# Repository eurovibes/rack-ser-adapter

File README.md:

<!-- SPDX-FileCopyrightText: 2021 Benedikt Spranger <b.spranger@linutronix.de> -->
<!-- SPDX-License-Identifier: CERN-OHL-S-2.0 -->

# rack-ser-adapter -  RS232 DE-9 to EIA-561 RJ45 adapter

## Adapter pinout (EIA-561)

### 1:1

| DB-9 Pin | Signal	| RJ45 |
|---------:|--------|-----:|
1 | DCD | 2
2 | RxD | 5
3 | TxD | 6
4 | DTR | 3
5 | GND | 4
6 | DSR | 1
7 | RTS | 8
8 | CTS | 7
9 |  -  | -

### CROSSOVER / NULLMODEM

| RJ45 | Signal	| DB-9 Pin |
|-----:|--------|---------:|
1 | DTR | 4
2 | DCD | -
3 | DST | 6
4 | GND | 5
5 | TxD | 3
6 | RxD | 2
7 | RTS | 7
8 | CTS | 8
9 |  -  | -

## License rules

rack-ser-adapter is provided under the terms of the CERN-OHL-S license
version 2 as provided in the LICENSES/CERN-OHL-S-2.0 file.

Instead of adding license boilerplates to the individual files,
rack-ser-adapter uses SPDX license identifiers, which are machine parseable
and considered legaly equivalent.

The SPDX license identifier in rack-ser-adapter shall be added at the first
possible line in a file which can contain a comment. This is normally the
first line except for scripts. Scripts require the #!PATH_TO_INTERPRETER tag
in the first line; place the SPDX identifier into the second line.

The SPDX license identifier is added in form of a comment.

## Copyright and License

> Copyright Benedikt Spranger 2021.
> This source describes Open Hardware and is licensed under the CERNOHL-S v2.
> You may redistribute and modify this source and make products using it
> under the terms of the CERN-OHL-S v2 (https://ohwr.org/cern ohl s v2.txt ).
> This source is distributed WITHOUT ANY EXPRESS OR IMPLIED WARRANTY, INCLUDING
> OF MERCHANTABILITY, SATISFACTORY QUALITY AND FITNESS FOR A PARTICULAR PURPOSE.
> Please see the CERN-OHL-S v2 for applicable conditions.
> Source location: https://github.com/eurovibes/rack-ser-adapter
> As per CERN-OHL-S v2 section 4, should You produce hardware based
> on this source, You must where practicable maintain the Source Location
> visible on the external case of the rack-ser-adapter or other products you
> make using this source.

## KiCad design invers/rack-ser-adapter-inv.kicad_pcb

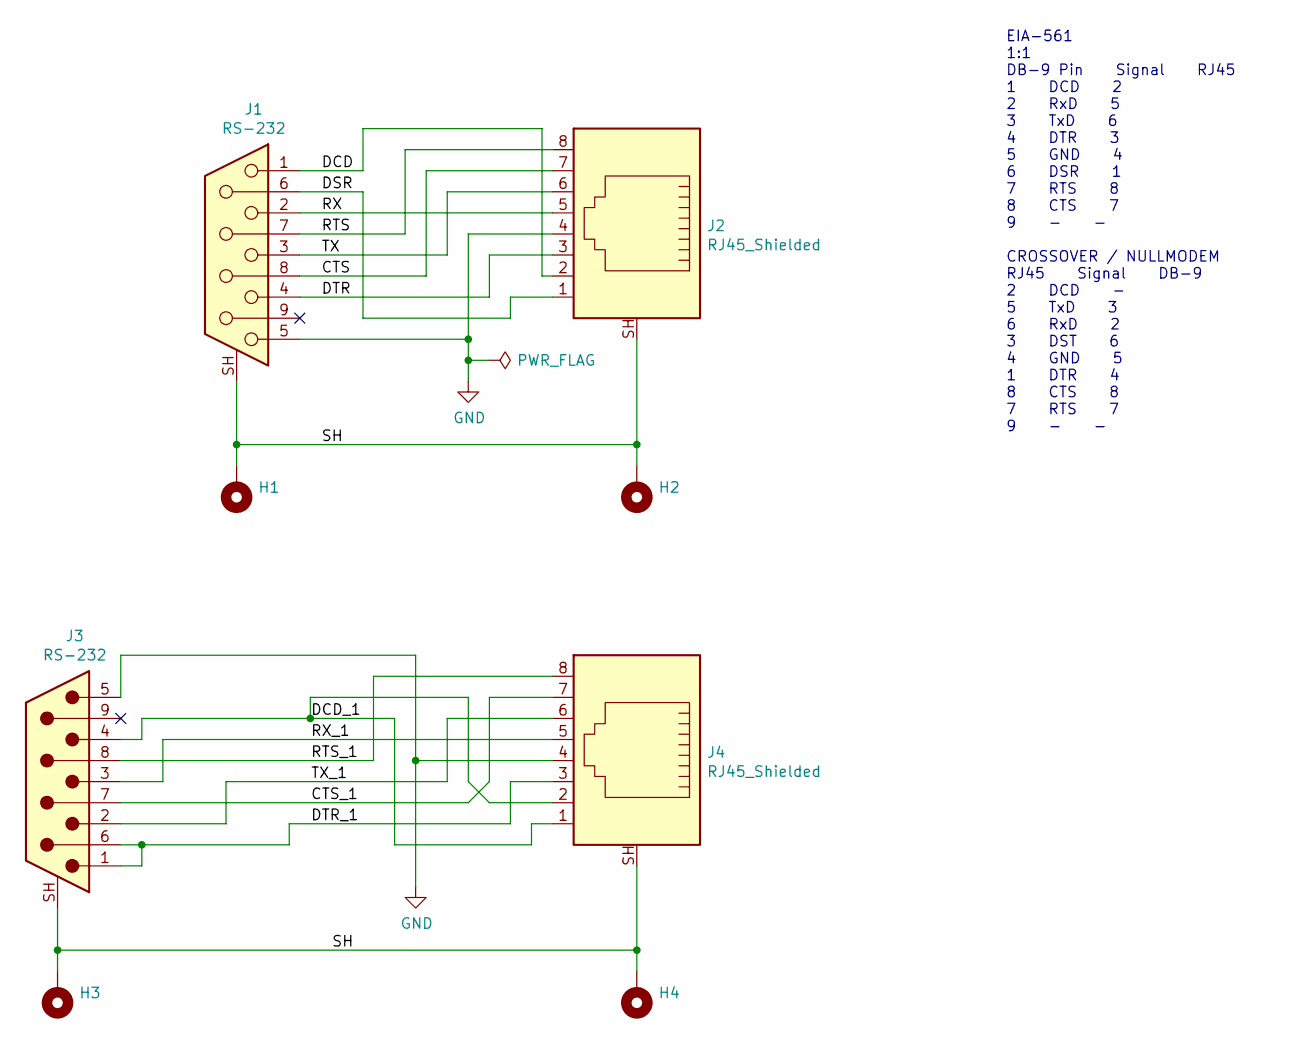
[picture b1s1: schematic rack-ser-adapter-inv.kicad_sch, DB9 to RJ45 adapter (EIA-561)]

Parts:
H1, H2, H3, H4: MountingHole_3.2mm_M3_ISO7380_Pad
J1: RS-232; DSUB-9_Female_Horizontal_P2.77x2.84mm_EdgePinOffset4.94mm_H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; ManuPart# A-DF 09 A/KG-T4S
J2, J4: RJ45_Shielded; RJ45_Ninigi_GE; ManuPart# MTJ-889X1-FSE
J3: RS-232; DSUB-9_Male_Horizontal_P2.77x2.84mm_EdgePinOffset4.94mm_Hou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; ManuPart# A-DS 09 A/KG-T4S

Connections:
/CTS: J1.8, J2.7
/CTS_1: J3.7, J4.7
/DCD: J1.1, J2.2
/DCD_1: J3.4, J4.1, J4.2
/DSR: J1.6, J2.1
/DTR: J1.4, J2.3
/DTR_1: J3.1, J3.6, J4.3
/RTS: J1.7, J2.8
/RTS_1: J3.8, J4.8
/RX: J1.2, J2.5
/RX_1: J3.3, J4.5
/SH: H1.1 (1_1), H2.1 (1_1), H3.1 (1_1), H4.1 (1_1), J1.SH (PAD), J2.SH, J3.SH (PAD), J4.SH
/TX: J1.3, J2.6
/TX_1: J3.2, J4.6
GND: J1.5, J2.4, J3.5, J4.4

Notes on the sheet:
EIA-561 1:1 DB-9 Pin Signal RJ45 1 DCD 2 2 RxD 5 3 TxD 6 4 DTR 3 5 GND 4 6 DSR 1 7 RTS 8 8 CTS 7 9 - - CROSSOVER / NULLMODEM RJ45 Signal DB-9 2 DCD - 5 TxD 3 6 RxD 2 3 DST 6 4 GND 5 1 DTR 4 8 CTS 8 7 RTS 7 9 - -

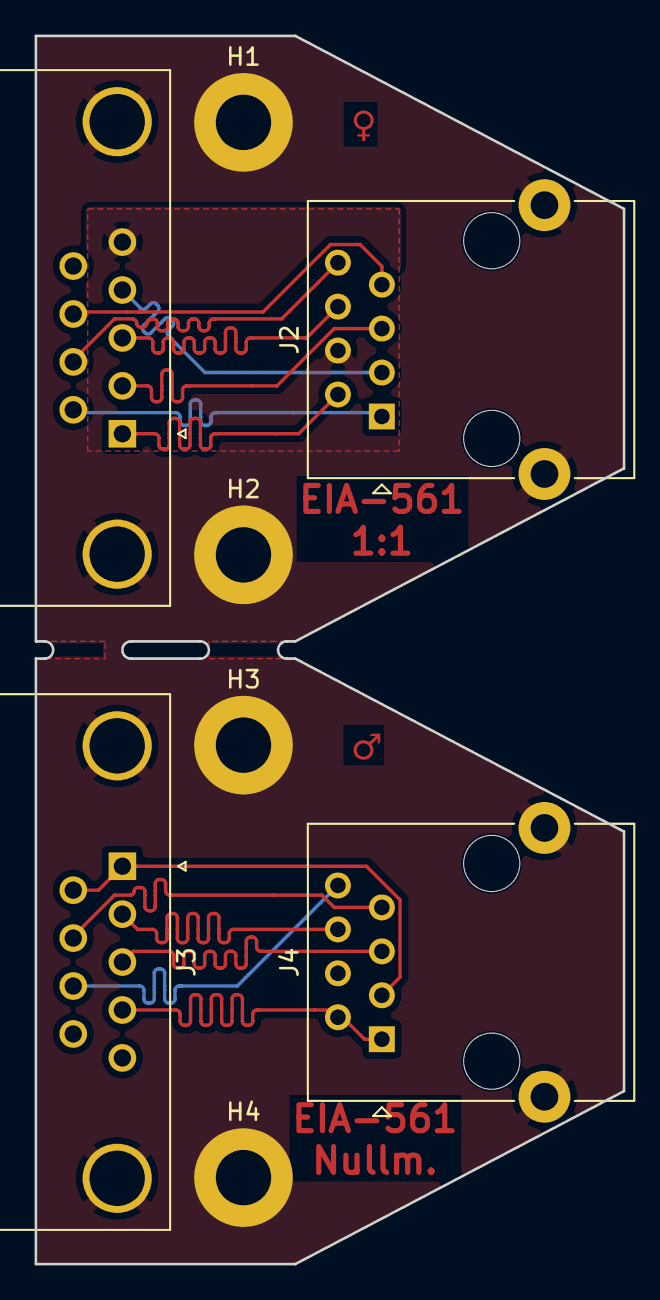
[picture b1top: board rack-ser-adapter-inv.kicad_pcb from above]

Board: 2 copper layers, 34.0 x 71.0 mm, 8 parts (0 on the bottom side), 15 nets.

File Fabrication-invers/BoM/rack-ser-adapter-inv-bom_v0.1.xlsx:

|  | KiBot Bill of Materials
 |  | Schematic: | rack-ser-adapter-inv | Component Groups: | 4
 |  | Variant: | default | Component Count: | 8
 |  | Revision: | v0.1 | Fitted Components: | 8
 |  | Date: | 2021-10-20 | Number of PCBs: | 1
 |  | KiCad Version: | 10.0.5-unknown-202607221313~667fa36054~ubuntu25.10.1 | Total Components: | 8
Row | Referencias | Parte | Valor | P/N | Fabricante | Cod. Digi-Key | Footprint | Descripción | Quantity Per PCB
1 | H1 H2 H3 H4 | MountingHole_Pad | ~ |  |  |  | MountingHole_3.2mm_M3_ISO7380_Pad |  | 4
2 | J2 J4 | RJ45_Shielded | RJ45_Shielded |  |  |  | RJ45_Ninigi_GE |  | 2
3 | J1 | DE9_Socket_MountingHoles | RS-232 |  |  |  | DSUB-9_Female_Horizontal_P2.77x2.84mm_EdgePinOffset4.94mm_Housed_MountingHolesO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 |  | 1
4 | J3 | DE9_Pins_MountingHoles | RS-232 |  |  |  | DSUB-9_Male_Horizontal_P2.77x2.84mm_EdgePinOffset4.94mm_Housed_MountingHolesOff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 |  | 1

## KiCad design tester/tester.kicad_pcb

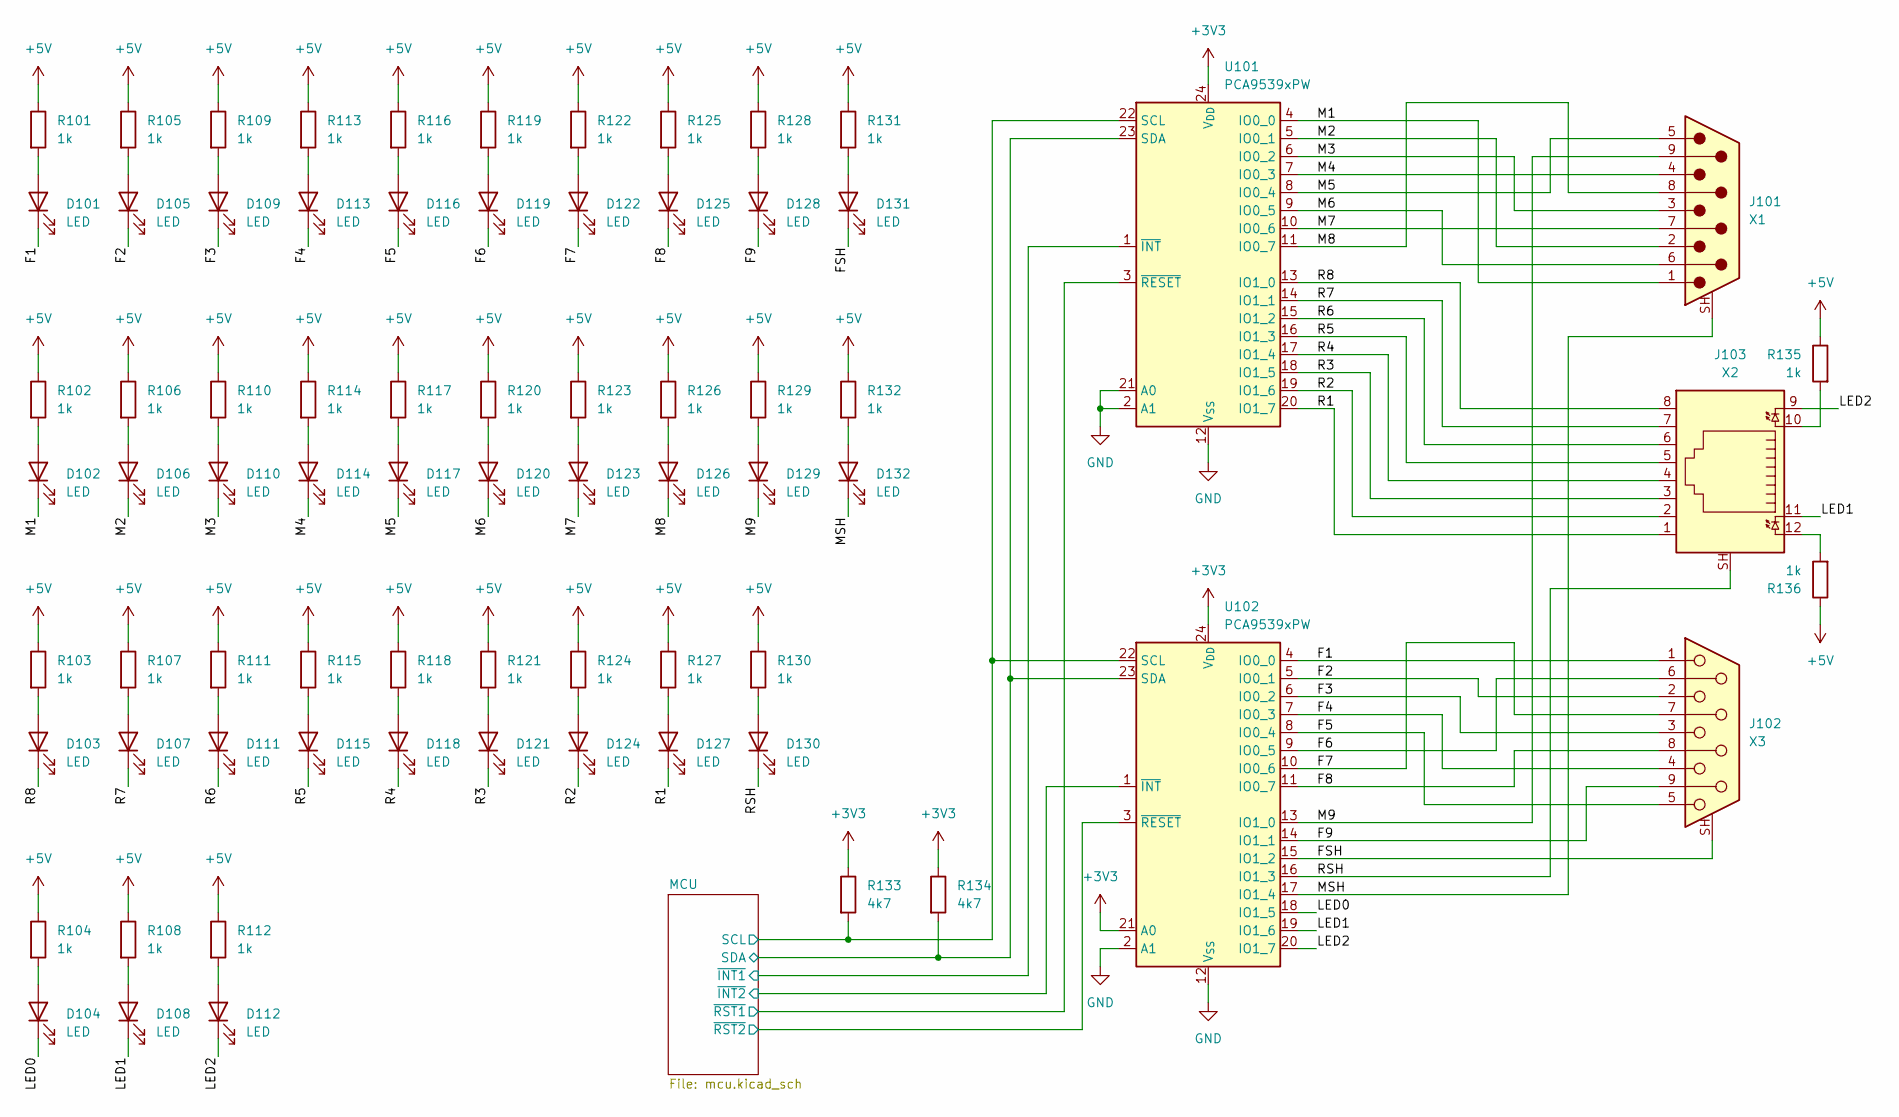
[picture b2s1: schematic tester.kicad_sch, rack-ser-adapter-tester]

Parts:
D101, D102, D103, D104, D105, D106, D107, D108, D109, D110, D111, D112, D113, D114, D115, D116, D117, D118, D119, D120, D121, D122, D123, D124, D125, D126, D127, D128, D129, D130, D131, D132: LED; LED_0603_1608Metric; mpn KT-0603W; LCSC# C2290
J101: X1; DSUB-9_Pins_Vertical_P2.77x2.84mm_MountingHoles; mpn DS1037-09MNAKT74-0CC
J102: X3; DSUB-9_Socket_Vertical_P2.77x2.84mm_MountingHoles; mpn DS1037-09FNAKT74-0CC
J103: X2; RJ45_Amphenol_RJHSE538X; mpn RJHSE5380
R101, R102, R103, R104, R105, R106, R107, R108, R109, R110, R111, R112, R113, R114, R115, R116, R117, R118, R119, R120, R121, R122, R123, R124, R125, R126, R127, R128, R129, R130, R131, R132, R135, R136: 1k; R_0402_1005Metric; mpn 0402WGF1001TCE; LCSC# C11702
R133, R134: 4k7; R_0402_1005Metric; mpn 0402WGF4701TCE; LCSC# C25900
U101, U102: PCA9539xPW; TSSOP-24_4.4x7.8mm_P0.65mm; mpn PCA9539PW; LCSC# C129516

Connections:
+3V3: R133.1, R134.1, U101.24 (V_{DD}), U102.21 (A0), U102.24 (V_{DD}); also elsewhere on the board
+5V: R101.1, R102.1, R103.1, R104.1, R105.1, R106.1, R107.1, R108.1, R109.1, R110.1, R111.1, R112.1, R113.1, R114.1, R115.1, R116.1, R117.1, R118.1, R119.1, R120.1, R121.1, R122.1, R123.1, R124.1, R125.1, R126.1, R127.1, R128.1, R129.1, R130.1, R131.1, R132.1, R135.1, R136.1; also elsewhere on the board
/F1: D101.1 (K), J102.1, U102.4 (IO0_0)
/F2: D105.1 (K), J102.2, U102.5 (IO0_1)
/F3: D109.1 (K), J102.3, U102.6 (IO0_2)
/F4: D113.1 (K), J102.4, U102.7 (IO0_3)
/F5: D116.1 (K), J102.5, U102.8 (IO0_4)
/F6: D119.1 (K), J102.6, U102.9 (IO0_5)
/F7: D122.1 (K), J102.7, U102.10 (IO0_6)
/F8: D125.1 (K), J102.8, U102.11 (IO0_7)
/F9: D128.1 (K), J102.9, U102.14 (IO1_1)
/FSH: D131.1 (K), J102.SH (PAD), U102.15 (IO1_2)
/LED0: D104.1 (K), U102.18 (IO1_5)
/LED1: D108.1 (K), J103.11, U102.19 (IO1_6)
/LED2: D112.1 (K), J103.9, U102.20 (IO1_7)
/M1: D102.1 (K), J101.1, U101.4 (IO0_0)
/M2: D106.1 (K), J101.2, U101.5 (IO0_1)
/M3: D110.1 (K), J101.3, U101.6 (IO0_2)
/M4: D114.1 (K), J101.4, U101.7 (IO0_3)
/M5: D117.1 (K), J101.5, U101.8 (IO0_4)
/M6: D120.1 (K), J101.6, U101.9 (IO0_5)
/M7: D123.1 (K), J101.7, U101.10 (IO0_6)
/M8: D126.1 (K), J101.8, U101.11 (IO0_7)
/M9: D129.1 (K), J101.9, U102.13 (IO1_0)
/MCU/SCL: R133.2, U101.22 (SCL), U102.22 (SCL); also elsewhere on the board
/MCU/SDA: R134.2, U101.23 (SDA), U102.23 (SDA); also elsewhere on the board
/MCU/~INT1: U101.1 (~INT); also elsewhere on the board
/MCU/~INT2: U102.1 (~INT); also elsewhere on the board
/MCU/~RST1: U101.3 (~RESET); also elsewhere on the board
/MCU/~RST2: U102.3 (~RESET); also elsewhere on the board
/MSH: D132.1 (K), J101.SH (PAD), U102.17 (IO1_4)
/R1: D127.1 (K), J103.1, U101.20 (IO1_7)
/R2: D124.1 (K), J103.2, U101.19 (IO1_6)
/R3: D121.1 (K), J103.3, U101.18 (IO1_5)
/R4: D118.1 (K), J103.4, U101.17 (IO1_4)
/R5: D115.1 (K), J103.5, U101.16 (IO1_3)
/R6: D111.1 (K), J103.6, U101.15 (IO1_2)
/R7: D107.1 (K), J103.7, U101.14 (IO1_1)
/R8: D103.1 (K), J103.8, U101.13 (IO1_0)
/RSH: D130.1 (K), J103.SH, U102.16 (IO1_3)
GND: U101.2 (A1), U101.12 (V_{SS}), U101.21 (A0), U102.2 (A1), U102.12 (V_{SS}); also elsewhere on the board
unnamed: D101.2 (A), R101.2
unnamed: D102.2 (A), R102.2
unnamed: D103.2 (A), R103.2
unnamed: D104.2 (A), R104.2
unnamed: D105.2 (A), R105.2
unnamed: D106.2 (A), R106.2
unnamed: D107.2 (A), R107.2
unnamed: D108.2 (A), R108.2
unnamed: D109.2 (A), R109.2
unnamed: D110.2 (A), R110.2
unnamed: D111.2 (A), R111.2
unnamed: D112.2 (A), R112.2
unnamed: D113.2 (A), R113.2
unnamed: D114.2 (A), R114.2
unnamed: D115.2 (A), R115.2
unnamed: D116.2 (A), R116.2
unnamed: D117.2 (A), R117.2
unnamed: D118.2 (A), R118.2
unnamed: D119.2 (A), R119.2
unnamed: D120.2 (A), R120.2
unnamed: D121.2 (A), R121.2
unnamed: D122.2 (A), R122.2
unnamed: D123.2 (A), R123.2
unnamed: D124.2 (A), R124.2
unnamed: D125.2 (A), R125.2
unnamed: D126.2 (A), R126.2
unnamed: D127.2 (A), R127.2
unnamed: D128.2 (A), R128.2
unnamed: D129.2 (A), R129.2
unnamed: D130.2 (A), R130.2
unnamed: D131.2 (A), R131.2
unnamed: D132.2 (A), R132.2
unnamed: J103.10, R135.2
unnamed: J103.12, R136.2

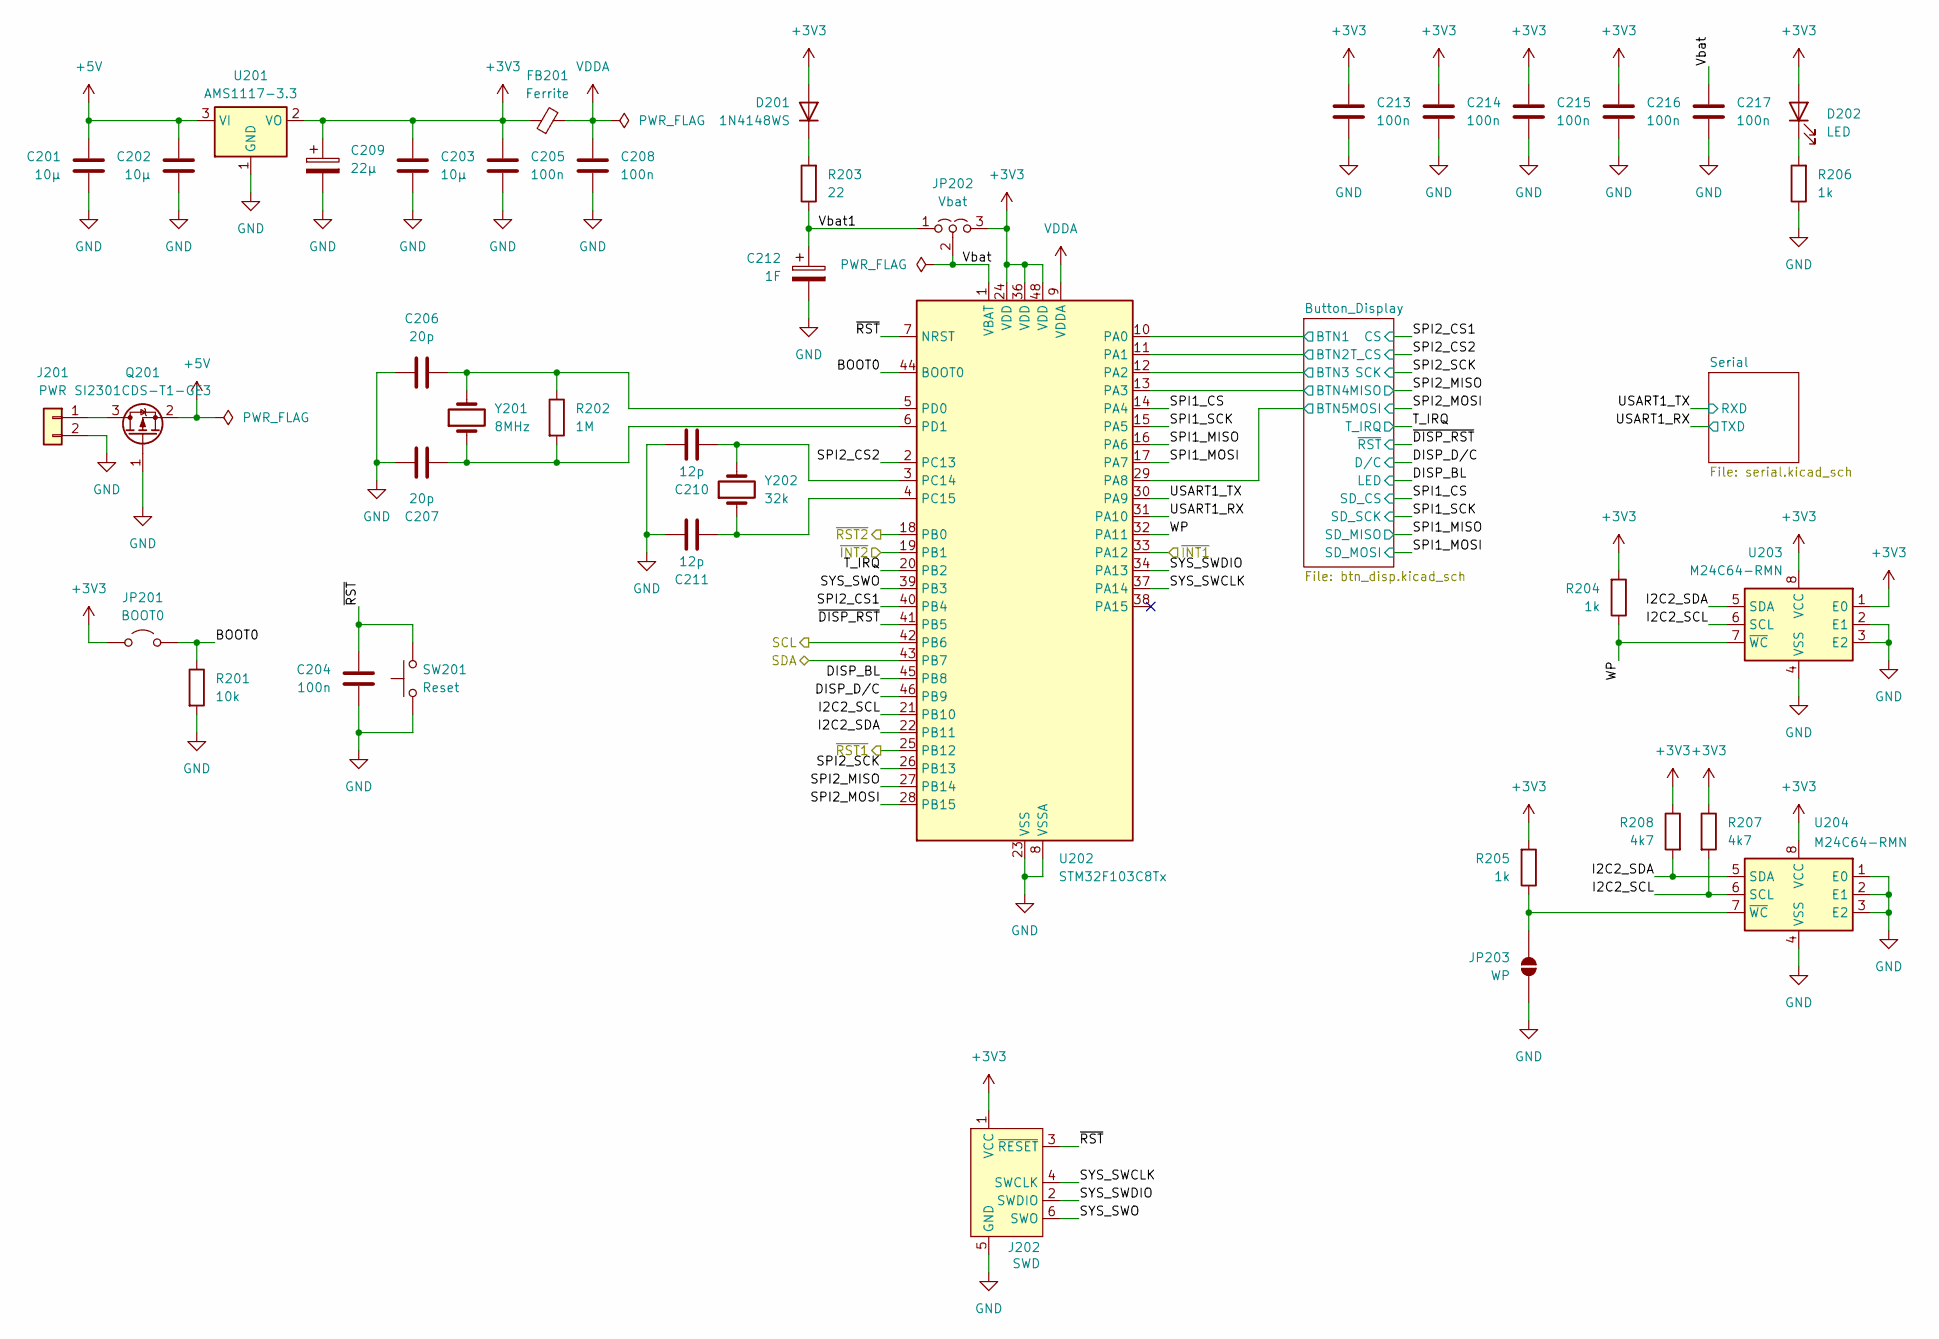
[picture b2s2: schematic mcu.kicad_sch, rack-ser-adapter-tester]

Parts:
C201, C202, C203: 10µ; C_0805_2012Metric; mpn CL21A106KAYNNNE; LCSC# C15850
C204, C205, C208, C213, C214, C215, C216, C217: 100n; C_0402_1005Metric; mpn CL05B104KB54PNC; LCSC# C307331
C206, C207: 20p; C_0402_1005Metric; mpn 0402CG200J500NT; LCSC# C1554
C209: 22µ; CP_EIA-3216-18_Kemet-A; mpn CA45-A-10V-22uF-K; LCSC# C129272
C210, C211: 12p; C_0402_1005Metric; mpn 0402CG120J500NT; LCSC# C1547
C212: 1F; CP_Radial_D8.0mm_P3.50mm
D201: 1N4148WS; D_SOD-123; mpn 1N4148W; LCSC# C81598
D202: LED; LED_0603_1608Metric; mpn KT-0603R; LCSC# C2286
FB201: Ferrite; L_0805_2012Metric; mpn GZ2012D101TF; LCSC# C1015
J201: PWR; TerminalBlock_WAGO_236-402_1x02_P5.00mm_45Degree
J202: SWD; Tag-Connect_TC2030-IDC-FP_2x03_P1.27mm_Vertical
JP201: BOOT0; SolderJumper-2_P1.3mm_Open_Pad1.0x1.5mm
JP202: Vbat; SolderJumper-3_P1.3mm_Open_Pad1.0x1.5mm
JP203: WP; SolderJumper-2_P1.3mm_Open_Pad1.0x1.5mm
Q201: SI2301CDS-T1-GE3; SOT-23; mpn SI2301CDS-T1-GE3; LCSC# C10487
R201: 10k; R_0402_1005Metric; mpn 0402WGF1002TCE; LCSC# C25744
R202: 1M; R_0402_1005Metric; mpn 0402WGF1004TCE; LCSC# C26083
R203: 22; R_1206_3216Metric; mpn 1206W4F220JT5E; LCSC# C17958
R204, R205, R206: 1k; R_0402_1005Metric; mpn 0402WGF1001TCE; LCSC# C11702
R207, R208: 4k7; R_0402_1005Metric; mpn 0402WGF4701TCE; LCSC# C25900
SW201: Reset; SW_PUSH_6mm; mpn TACT-65R-F
U201: AMS1117-3.3; SOT-223-3_TabPin2; mpn AMS1117-3.3; LCSC# C6186
U202: STM32F103C8Tx; LQFP-48_7x7mm_P0.5mm; mpn STM32F103C8T6; LCSC# C8734
U203, U204: M24C64-RMN; SOIC-8_3.9x4.9mm_P1.27mm; mpn M24C64-RMN6TP; LCSC# C79988
Y201: 8MHz; Crystal_SMD_5032-2Pin_5.0x3.2mm; mpn X50328MSB2GI; LCSC# C115962
Y202: 32k; Crystal_SMD_3215-2Pin_3.2x1.5mm; mpn Q13FC13500004; LCSC# C32346

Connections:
+3V3: C203.1, C205.1, C209.1, C213.1, C214.1, C215.1, C216.1, D201.2 (A), D202.2 (A), FB201.1, J202.1 (VCC), JP201.1 (A), JP202.3 (B), R204.2, R205.2, R207.1, R208.1, U201.2 (VO), U202.24 (VDD), U202.36 (VDD), U202.48 (VDD), U203.1 (E0), U203.8 (VCC), U204.8 (VCC); also elsewhere on the board
+5V: C201.1, C202.1, Q201.2 (S), U201.3 (VI); also elsewhere on the board
/MCU/BOOT0: JP201.2 (B), R201.1, U202.44 (BOOT0)
/MCU/Button_Display/BTN1: U202.10 (PA0); also elsewhere on the board
/MCU/Button_Display/BTN2: U202.11 (PA1); also elsewhere on the board
/MCU/Button_Display/BTN3: U202.12 (PA2); also elsewhere on the board
/MCU/Button_Display/BTN4: U202.13 (PA3); also elsewhere on the board
/MCU/Button_Display/BTN5: U202.29 (PA8); also elsewhere on the board
/MCU/DISP_BL: U202.45 (PB8); also elsewhere on the board
/MCU/DISP_D/C: U202.46 (PB9); also elsewhere on the board
/MCU/I2C2_SCL: R207.2, U202.21 (PB10), U203.6 (SCL), U204.6 (SCL)
/MCU/I2C2_SDA: R208.2, U202.22 (PB11), U203.5 (SDA), U204.5 (SDA)
/MCU/SCL: U202.42 (PB6); also elsewhere on the board
/MCU/SDA: U202.43 (PB7); also elsewhere on the board
/MCU/SPI1_CS: U202.14 (PA4); also elsewhere on the board
/MCU/SPI1_MISO: U202.16 (PA6); also elsewhere on the board
/MCU/SPI1_MOSI: U202.17 (PA7); also elsewhere on the board
/MCU/SPI1_SCK: U202.15 (PA5); also elsewhere on the board
/MCU/SPI2_CS1: U202.40 (PB4); also elsewhere on the board
/MCU/SPI2_CS2: U202.2 (PC13); also elsewhere on the board
/MCU/SPI2_MISO: U202.27 (PB14); also elsewhere on the board
/MCU/SPI2_MOSI: U202.28 (PB15); also elsewhere on the board
/MCU/SPI2_SCK: U202.26 (PB13); also elsewhere on the board
/MCU/SYS_SWCLK: J202.4 (SWCLK), U202.37 (PA14)
/MCU/SYS_SWDIO: J202.2 (SWDIO), U202.34 (PA13)
/MCU/SYS_SWO: J202.6 (SWO), U202.39 (PB3)
/MCU/T_IRQ: U202.20 (PB2); also elsewhere on the board
/MCU/USART1_RX: U202.31 (PA10); also elsewhere on the board
/MCU/USART1_TX: U202.30 (PA9); also elsewhere on the board
/MCU/Vbat: C217.1, JP202.2 (C), U202.1 (VBAT)
/MCU/Vbat1: C212.1, JP202.1 (A), R203.1
/MCU/WP: R204.1, U202.32 (PA11), U203.7 (~WC)
/MCU/~DISP_RST: U202.41 (PB5); also elsewhere on the board
/MCU/~INT1: U202.33 (PA12); also elsewhere on the board
/MCU/~INT2: U202.19 (PB1); also elsewhere on the board
/MCU/~RST1: U202.25 (PB12); also elsewhere on the board
/MCU/~RST2: U202.18 (PB0); also elsewhere on the board
/MCU/~RST: C204.1, J202.3 (~RESET), SW201.2, U202.7 (NRST)
GND: C201.2, C202.2, C203.2, C204.2, C205.2, C206.1, C207.1, C208.2, C209.2, C210.1, C211.1, C212.2, C213.2, C214.2, C215.2, C216.2, C217.2, J201.2, J202.5 (GND), JP203.1 (A), Q201.1 (G), R201.2, R206.1, SW201.1, U201.1 (GND), U202.8 (VSSA), U202.23 (VSS), U202.35 (VSS), U202.47 (VSS), U203.2 (E1), U203.3 (E2), U203.4 (VSS), U204.1 (E0), U204.2 (E1), U204.3 (E2), U204.4 (VSS); also elsewhere on the board
unnamed: D201.1 (K), R203.2
unnamed: D202.1 (K), R206.2
unnamed: J201.1, Q201.3 (D)
unnamed: JP203.2 (B), R205.1, U204.7 (~WC)
unnamed: C210.2, U202.3 (PC14), Y202.2
unnamed: C211.2, U202.4 (PC15), Y202.1
unnamed: C206.2, R202.1, U202.5 (PD0), Y201.2
unnamed: C207.2, R202.2, U202.6 (PD1), Y201.1
VDDA: C208.1, FB201.2, U202.9 (VDDA)

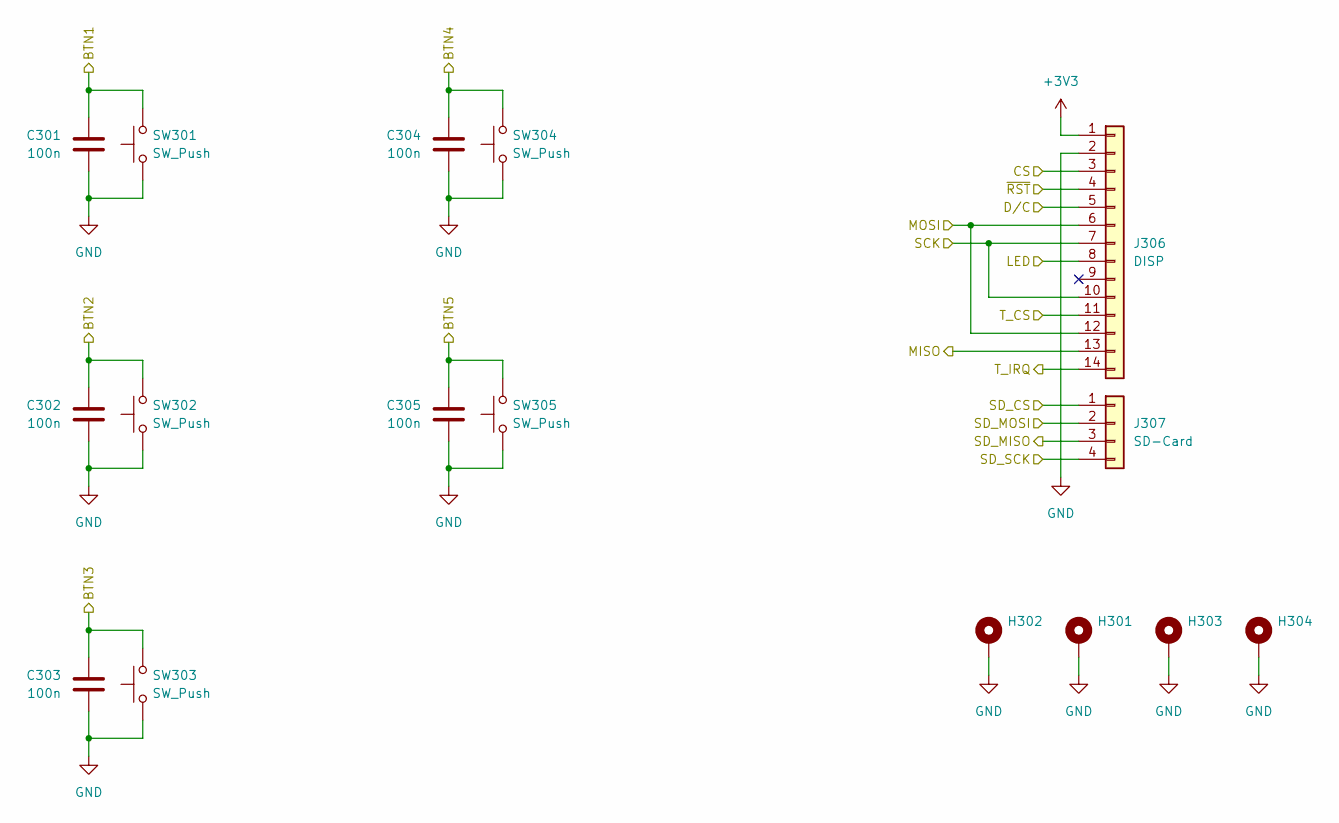
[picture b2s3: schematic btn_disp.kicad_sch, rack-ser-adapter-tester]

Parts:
C301, C302, C303, C304, C305: 100n; C_0402_1005Metric; mpn CL05B104KB54PNC; LCSC# C307331
H301, H302, H303, H304: MountingHole_3.2mm_M3_ISO14580_Pad
J306: DISP; PinHeader_1x14_P2.54mm_Vertical
J307: SD-Card; PinHeader_1x04_P2.54mm_Vertical
SW301, SW302, SW303, SW304, SW305: SW_Push; TS-1187A-B-A-B; mpn TS-1187A-B-A-B; LCSC# C318884

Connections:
+3V3: J306.1; also elsewhere on the board
/MCU/Button_Display/BTN1: C301.1, SW301.2; also elsewhere on the board
/MCU/Button_Display/BTN2: C302.1, SW302.2; also elsewhere on the board
/MCU/Button_Display/BTN3: C303.1, SW303.2; also elsewhere on the board
/MCU/Button_Display/BTN4: C304.1, SW304.2; also elsewhere on the board
/MCU/Button_Display/BTN5: C305.1, SW305.2; also elsewhere on the board
/MCU/DISP_BL: J306.8; also elsewhere on the board
/MCU/DISP_D/C: J306.5; also elsewhere on the board
/MCU/SPI1_CS: J307.1; also elsewhere on the board
/MCU/SPI1_MISO: J307.3; also elsewhere on the board
/MCU/SPI1_MOSI: J307.2; also elsewhere on the board
/MCU/SPI1_SCK: J307.4; also elsewhere on the board
/MCU/SPI2_CS1: J306.3; also elsewhere on the board
/MCU/SPI2_CS2: J306.11; also elsewhere on the board
/MCU/SPI2_MISO: J306.13; also elsewhere on the board
/MCU/SPI2_MOSI: J306.6, J306.12; also elsewhere on the board
/MCU/SPI2_SCK: J306.7, J306.10; also elsewhere on the board
/MCU/T_IRQ: J306.14; also elsewhere on the board
/MCU/~DISP_RST: J306.4; also elsewhere on the board
GND: C301.2, C302.2, C303.2, C304.2, C305.2, H301.1 (1_1), H302.1 (1_1), H303.1 (1_1), H304.1 (1_1), J306.2, SW301.1, SW302.1, SW303.1, SW304.1, SW305.1; also elsewhere on the board

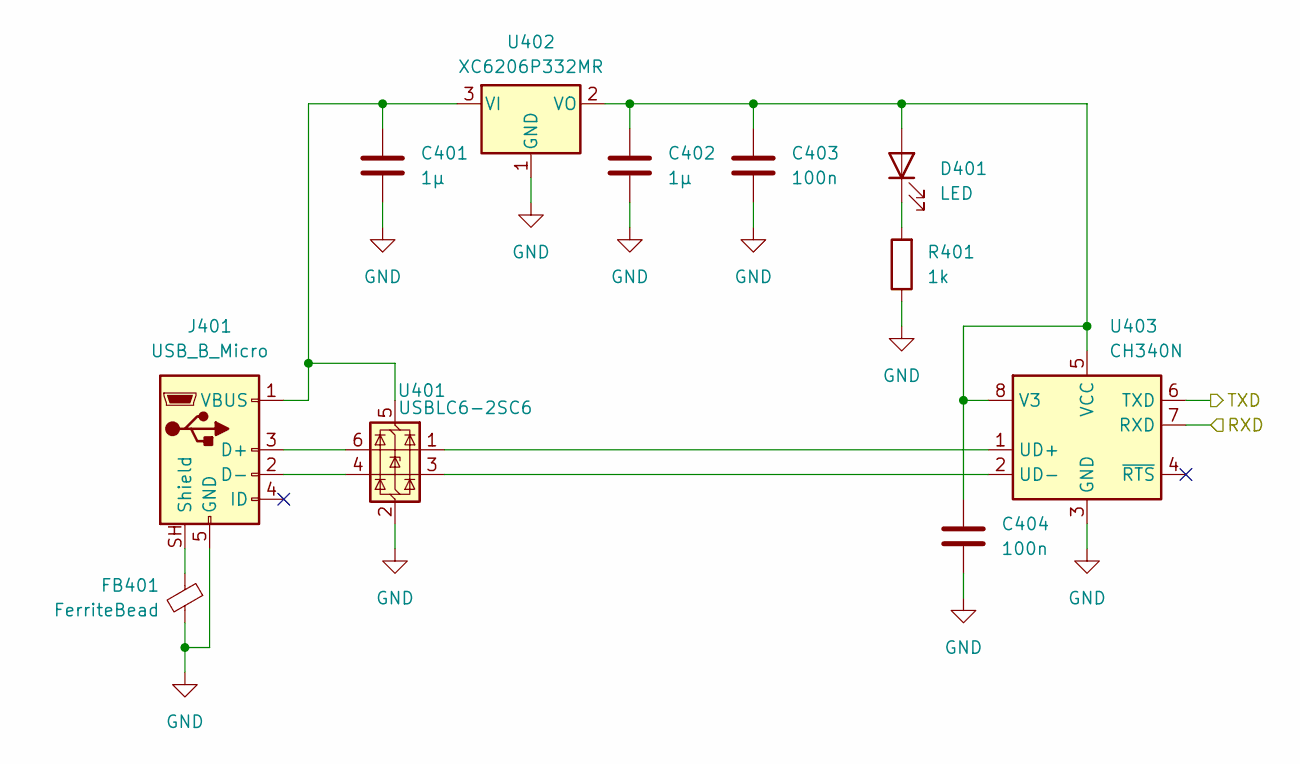
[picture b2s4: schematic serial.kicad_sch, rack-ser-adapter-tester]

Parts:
C401, C402: 1µ; C_0603_1608Metric; mpn CL10A105KB8NNNC; LCSC# C15849
C403, C404: 100n; C_0402_1005Metric; mpn CL05B104KB54PNC; LCSC# C307331
D401: LED; LED_0603_1608Metric; mpn KT-0603R; LCSC# C2286
FB401: FerriteBead; L_0603_1608Metric; mpn GZ1608D601TF; LCSC# C1002
J401: USB_B_Micro; USB_Micro-B_Amphenol_10118193-0001LF_Horizontal; mpn 10118193-0001LF; LCSC# C132562
R401: 1k; R_0402_1005Metric; mpn 0402WGF1001TCE; LCSC# C11702
U401: USBLC6-2SC6; SOT-23-6; mpn USBLC6-2SC6; LCSC# C2827654
U402: XC6206P332MR; SOT-23-3; mpn XC6206P332MR-G; LCSC# C5446
U403: CH340N; JEITA_SOIC-8_3.9x4.9mm_P1.27mm; mpn CH340N; LCSC# C2977777

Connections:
/MCU/USART1_RX: U403.6 (TXD); also elsewhere on the board
/MCU/USART1_TX: U403.7 (RXD); also elsewhere on the board
GND: C401.2, C402.2, C403.2, C404.2, FB401.2, J401.5 (GND), R401.1, U401.2 (GND), U402.1 (GND), U403.3 (GND); also elsewhere on the board
unnamed: C402.1, C403.1, C404.1, D401.2 (A), U402.2 (VO), U403.5 (VCC), U403.8 (V3)
unnamed: D401.1 (K), R401.2
unnamed: J401.3 (D+), U401.6 (I/O1)
unnamed: J401.2 (D-), U401.4 (I/O2)
unnamed: FB401.1, J401.SH (Shield)
unnamed: C401.1, J401.1 (VBUS), U401.5 (VBUS), U402.3 (VI)
unnamed: U401.1 (I/O1), U403.1 (UD+)
unnamed: U401.3 (I/O2), U403.2 (UD-)

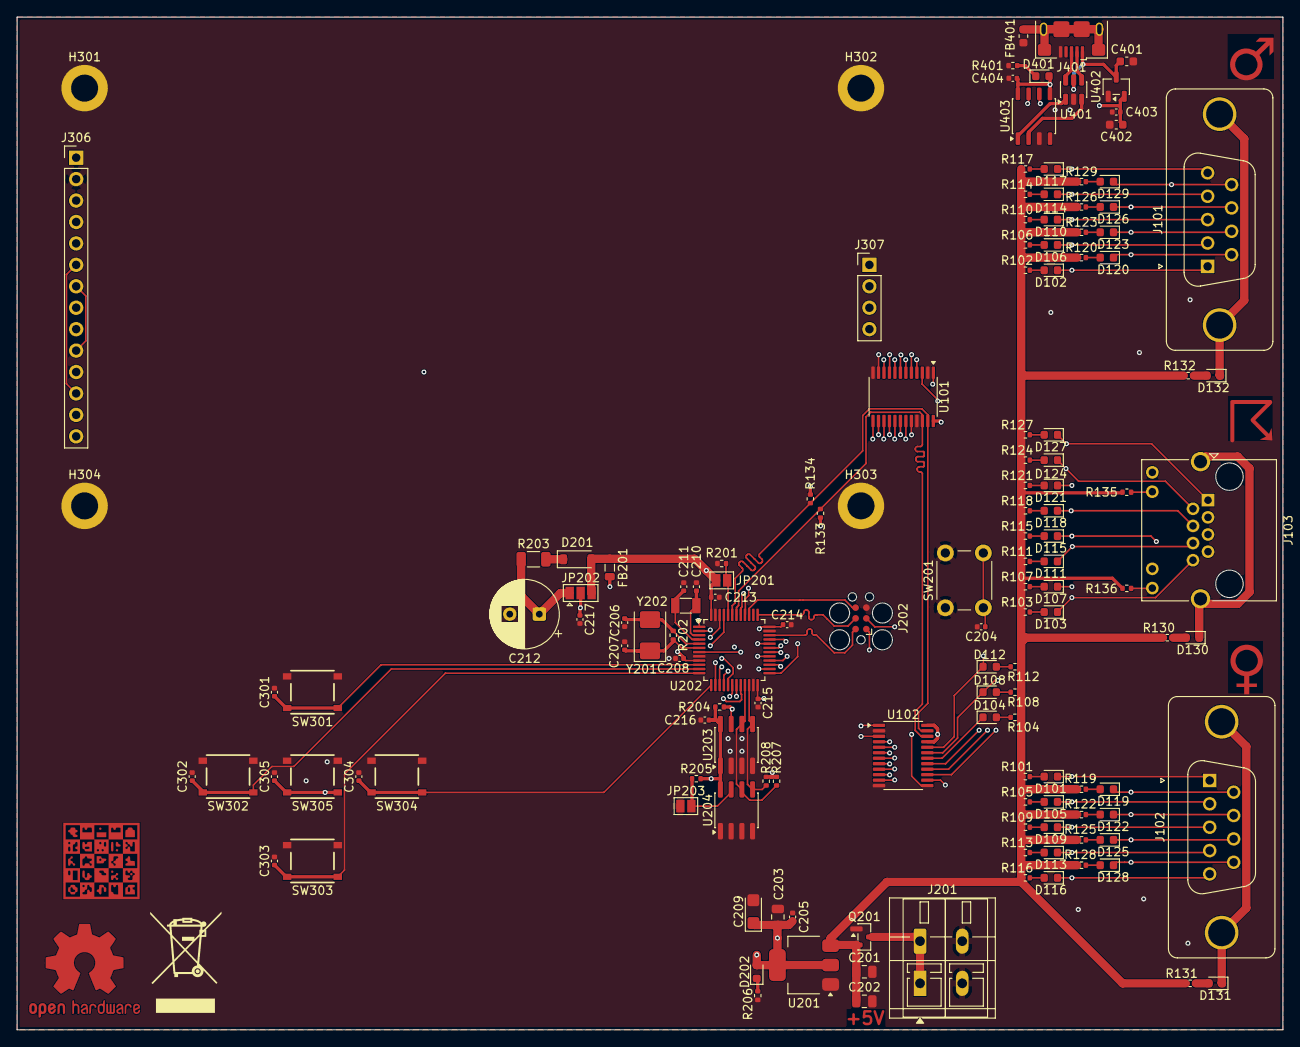
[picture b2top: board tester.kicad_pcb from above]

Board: 4 copper layers, 150.0 x 120.0 mm, 141 parts (0 on the bottom side), 122 nets.

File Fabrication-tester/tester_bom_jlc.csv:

"Comment","Designator","Footprint","LCSC Part #"
"12p","C210,C211","C_0402_1005Metric","C1547"
"20p","C206,C207","C_0402_1005Metric","C1554"
"100n","C204,C205,C208,C213,C214,C215,C216,C217,C301,C302,C303,C304,C305,C403,C404","C_0402_1005Metric","C307331"
"1µ","C401,C402","C_0603_1608Metric","C15849"
"10µ","C201,C202,C203","C_0805_2012Metric","C15850"
"1N4148WS","D201","D_SOD-123","C2128"
"LED","D101,D102,D103,D104,D105,D106,D107,D108,D109,D110,D111,D112,D113,D114,D115,D116,D117,D118,D119,D120,D121,D122,D123,D124,D125,D126,D127,D128,D129,D130,D131,D132,D202,D401","LED_0603_1608Metric","C2290 C2286"
"Ferrite","FB201","L_0805_2012Metric","C1015"
"FerriteBead","FB401","L_0603_1608Metric","C1002"
"USB_B_Micro","J401","USB_Micro-B_Amphenol_10118193-0001LF_Horizontal","C132563"
"SI2301CDS-T1-GE3","Q201","SOT-23","C10487"
"22","R203","R_1206_3216Metric","C17958"
"1k","R101,R102,R103,R104,R105,R106,R107,R108,R109,R110,R111,R112,R113,R114,R115,R116,R117,R118,R119,R120,R121,R122,R123,R124,R125,R126,R127,R128,R129,R130,R131,R132,R204,R205,R206,R401","R_0402_1005Metric","C11702"
"4k7","R133,R134","R_0402_1005Metric","C25900"
"10k","R201","R_0402_1005Metric","C25744"
"1M","R202","R_0402_1005Metric","C26083"
"SW_Push","SW301,SW302,SW303,SW304,SW305","TS-1187A-B-A-B","C318884"
"AMS1117-3.3","U201","SOT-223-3_TabPin2","C6186"
"CH340N","U403","JEITA_SOIC-8_3.9x4.9mm_P1.27mm","C2977777"
"M24C64-RMN","U203,U204","SOIC-8_3.9x4.9mm_P1.27mm","C79988"
"PCA9539xPW","U101,U102","TSSOP-24_4.4x7.8mm_P0.65mm","C129516"
"STM32F103C8Tx","U202","LQFP-48_7x7mm_P0.5mm","C8734"
"USBLC6-2SC6","U401","SOT-23-6","C2827654"
"XC6206P332MR","U402","SOT-23-3","C5446"
"32k","Y202","Crystal_SMD_3215-2Pin_3.2x1.5mm","C32346"
"8MHz","Y201","Crystal_SMD_5032-2Pin_5.0x3.2mm","C115962"

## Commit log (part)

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2021-10-30 Initial
2021-10-30 Initial gh-pages commit
2021-10-30 Deploying to gh-pages from @ eurovibes/rack-ser-adapter@6b66311859c8c63105e36cc5bb5a7ae5f46a8007 🚀
2021-10-30 Deploying to gh-pages from @ eurovibes/rack-ser-adapter@75658229729c2af477a508b3d2887cf0b11bceea 🚀
2021-11-01 Change breakaway tabs width
2021-11-01 Deploying to gh-pages from @ eurovibes/rack-ser-adapter@522a9e39df5aa036cf46db45d9ab01711437a7d1 🚀
2021-11-01 Edit BOM
2021-11-01 Deploying to gh-pages from @ eurovibes/rack-ser-adapter@f0f49511e91ba7b544a9eecc005a680fe9f0ce58 🚀
2021-11-16 Add enclosure

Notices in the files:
invers/rack-ser-adapter-inv.kicad_pcb:
This work is licensed under the CERN-OHL-S v2
